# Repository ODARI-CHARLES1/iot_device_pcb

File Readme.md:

# IoT Device PCB

An IoT device PCB designed for logging and transmitting data.

## Schematic

## Specifications

- **Version:** V1.0.0
- **Date:** 2026-04-08
- **Company:** ODARI-DESIGNS

## Key Components

- **U1:** MCP73871 - Li-Ion/Li-Po Battery Charge Management Controller
- **J1:** USB Type-C Receptacle (USB 2.0, 16-pin)
- **J:** JST B2B-PH-K-S Connector (2-pin battery connection)
- **LEDs:** Status indicators (LTST-C170KRKT)

## Features

- USB-C power input
- Battery charging circuit (single-cell Li-Ion/Li-Po)
- LED status indicators
- Compact design for IoT applications

## License

MIT

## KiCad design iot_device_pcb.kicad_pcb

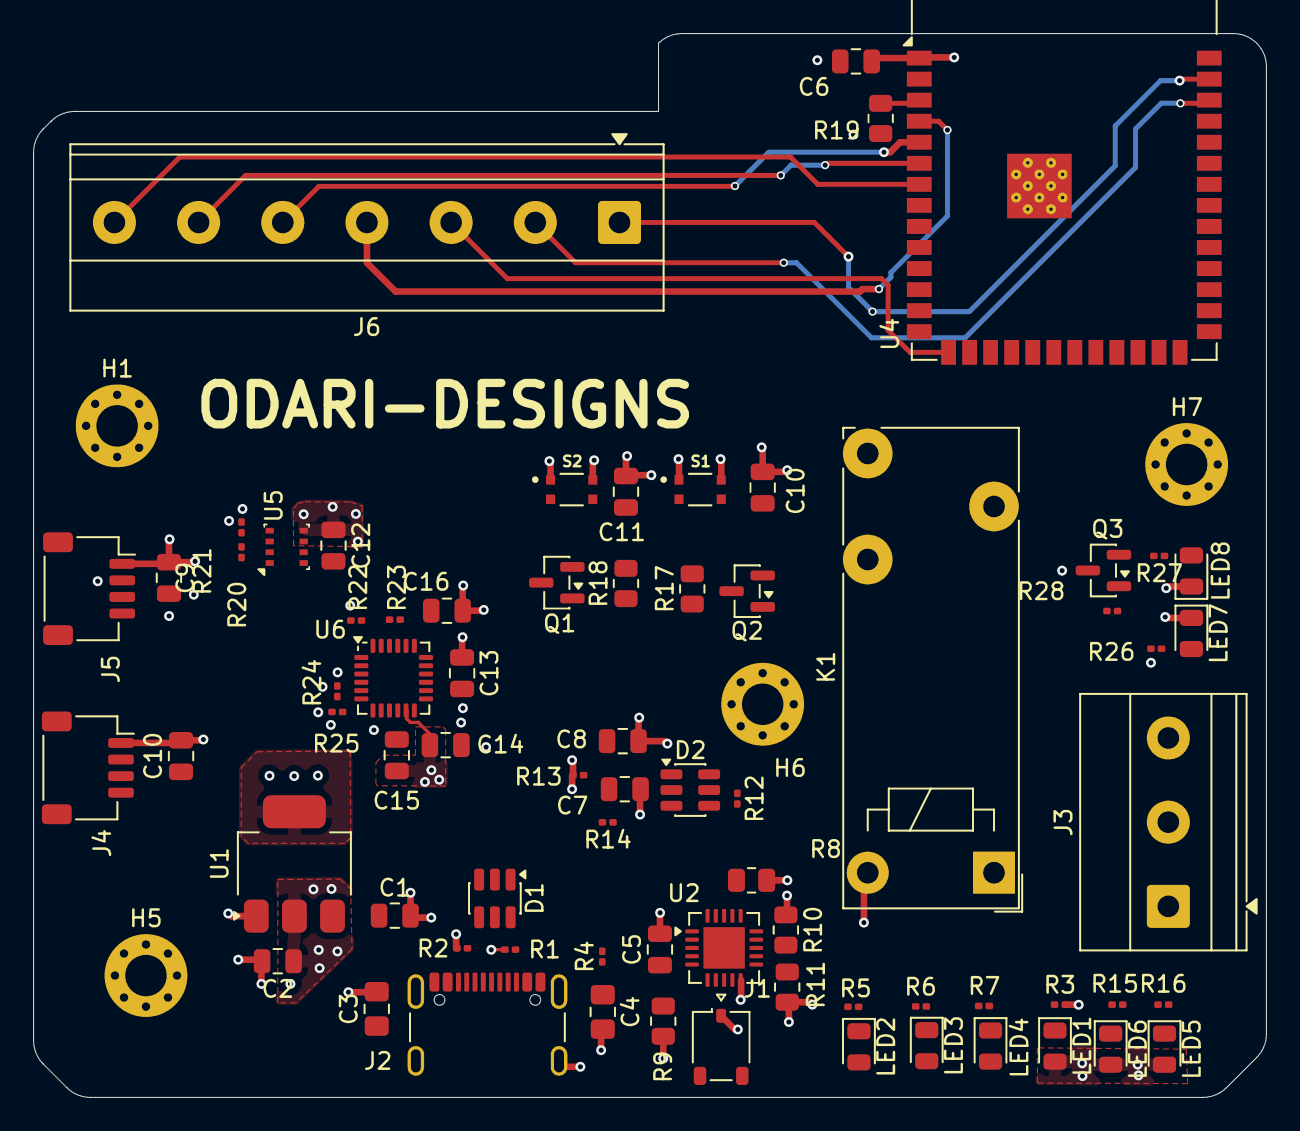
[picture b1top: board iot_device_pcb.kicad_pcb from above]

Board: 4 copper layers, 74.4 x 64.2 mm, 76 parts (0 on the bottom side), 49 nets.

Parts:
C1: 10u; C_0805_2012Metric
C2: 22u; C_0805_2012Metric
C3, C4: 470n; C_0805_2012Metric_Pad1.18x1.45mm_HandSolder
C5, C6, C8, C9, C10, C10#2, C12, C13, C14, C15: 0.1u; C_0805_2012Metric
C7, C11: 1u; C_0805_2012Metric
C16: 220p; C_0805_2012Metric
D1, D2: USBLC6-2SC6; SOT-23-6
H1, H5, H6, H7: MountingHole; MountingHole_2.5mm_Pad_Via
J1: B2B-PH-K-S_LF__SN_; JST_ACH_BM01B-ACHSS-A-GAN-ETF_1x01-1MP_P1.20mm_Vertical
J2: USB_C_Receptacle_USB2.0_16P; USB_C_Receptacle_GCT_USB4105-xx-A_16P_TopMnt_Horizontal
J3: Screw_Terminal_01x03; TerminalBlock_Phoenix_MKDS-1,5-3-5.08_1x03_P5.08mm_Horizont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
J4, J5: Conn_01x04_Pin; JST_SH_SM04B-SRSS-TB_1x04-1MP_P1.00mm_Horizontal
J6: Conn_01x07_Pin; TerminalBlock_Phoenix_MKDS-1,5-7-5.08_1x07_P5.08mm_Horizont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
K1: RAYEX-L90; Relay_1-Form-C_Schrack-RYII_RM3.2mm
LED1, LED4: LTST-C170KRKT; LED_0805_2012Metric
LED2, LED3, LED5, LED6, LED7, LED8: LTST-C170KGKT; LED_0805_2012Metric
Q1, Q2, Q3: BC817; SOT-23
R1, R2: 5.1k; R_0201_0603Metric
R3, R5, R6, R7, R15, R16, R26, R27, R28: 470R; R_0201_0603Metric
R4: 0; R_0201_0603Metric
R8, R9, R10, R11, R17, R18, R19: 10K; R_0805_2012Metric
R12: 22.1K; R_0201_0603Metric
R13, R24, R25: 47K5; R_0201_0603Metric
R14: 1k; R_0201_0603Metric
R20, R21, R22, R23: 4.7K; R_0201_0603Metric
S1, S2: USLPT2819DT2TR; SW_USLPT2819DT2TR
U1: AMS1117-3.3; SOT-223-3_TabPin2
U2: MCP73871; QFN-20-1EP_4x4mm_P0.5mm_EP2.5x2.5mm
U4: ESP32-S3-WROOM-1
U5: BME280; Bosch_LGA-8_2.5x2.5mm_P0.65mm_ClockwisePinNumbering
U6: MPU-6050; InvenSense_QFN-24_4x4mm_P0.5mm

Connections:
+3.3V: C2.1, C6.1, C8.2, C9.1, C10#2.1, C12.1, C13.1, C14.1, J4.2, J5.2, LED1.2, LED5.2, LED6.2, Q3.3 (C), R14.1, R19.1, R20.2, R21.2, R22.1, R23.1, R24.2, R25.2, R26.2, U1.2 (VO), U4.2 (3V3), U5.2 (CSB), U5.5 (SDO), U5.6 (VDDIO), U5.8 (VDD), U6.8 (VLOGIC), U6.13 (VDD)
+5V: C1.1, C4.1, LED2.2, LED3.2, LED4.2, R4.1, U1.3 (VI), U2.1 (OUT), U2.5 (THERM), U2.20 (OUT)
/Microcontroller-ESP32-S3-WROOM-1/BOOT: C10.1, Q2.2 (E), S1.3, S1.4, U4.27 (IO0)
/Microcontroller-ESP32-S3-WROOM-1/EN: C11.1, Q1.3 (C), R19.2, S2.3, S2.4, U4.3 (EN)
/Microcontroller-ESP32-S3-WROOM-1/GPIO1: J6.1, U4.39 (IO1)
/Microcontroller-ESP32-S3-WROOM-1/GPIO2: J6.2, U4.38 (IO2)
/Microcontroller-ESP32-S3-WROOM-1/GPIO3: J6.3, U4.15 (IO3)
/Microcontroller-ESP32-S3-WROOM-1/GPIO4: J6.4, U4.4 (IO4)
/Microcontroller-ESP32-S3-WROOM-1/GPIO5: J6.5, U4.5 (IO5)
/Microcontroller-ESP32-S3-WROOM-1/GPIO6: J6.6, U4.6 (IO6)
/Microcontroller-ESP32-S3-WROOM-1/GPIO7: J6.7, U4.7 (IO7)
/Microcontroller-ESP32-S3-WROOM-1/INT: U4.19 (IO11), U6.12 (INT)
/Microcontroller-ESP32-S3-WROOM-1/RELAY_FAN_GPIO: R28.2, U4.18 (IO10)
/Microcontroller-ESP32-S3-WROOM-1/RTS: Q1.2 (E), R18.2
/Microcontroller-ESP32-S3-WROOM-1/SCL: J4.4, J5.4, R21.1, R23.2, U4.17 (IO9), U5.4 (SCK), U6.23 (SCL)
/Microcontroller-ESP32-S3-WROOM-1/SDA: J4.3, J5.3, R20.1, R22.2, U4.12 (IO8), U5.3 (SDI), U6.24 (SDA)
/Microcontroller-ESP32-S3-WROOM-1/Sensors/XCL: R25.1, U6.7 (AUX_CL)
/Microcontroller-ESP32-S3-WROOM-1/Sensors/XDA: R24.1, U6.6 (AUX_DA)
/USBD+: D1.4 (I/O2), J2.B5 (CC2), R1.2
/USBD-: D1.6 (I/O1), D2.1 (I/O1), D2.3 (I/O2), J2.A5 (CC1), Q2.3 (C), R2.2, R17.2, U4.13 (USB_D-), U4.14 (USB_D+)
/VBAT: U2.14 (V_{BAT}), U2.15 (V_{BAT}), U2.16 (V_{BAT_SENSE})
GND: C1.2, C2.2, C3.2, C4.2, C5.2, C6.2, C7.2, C8.1, C9.2, C10.2, C10#2.2, C11.2, C12.2, C13.2, C14.2, C15.2, C16.2, D1.2 (GND), D2.2 (GND), J1.1 (1_1), J2.A1 (GND), J2.A12 (GND), J2.B1 (GND), J2.B12 (GND), J2.S1 (SHIELD), J4.1, J5.1, K1.A2, LED7.1, LED8.1, R1.1, R2.1, R3.1, R8.2, R9.2, R10.1, R11.1, R13.2, S1.1, S1.2, S2.1, S2.2, U1.1 (GND), U2.3 (SEL), U2.10 (V_{SS}), U2.11 (V_{SS}), U2.21 (V_{SS}), U4.1 (GND), U4.40 (GND), U4.41 (GND), U5.1 (GND), U5.7 (GND), U6.1 (CLKIN), U6.9 (AD0), U6.11 (FSYNC), U6.18 (GND)
unnamed: D1.1 (I/O1), J2.A7 (D-), J2.B7 (D-)
unnamed: D1.3 (I/O2), J2.A6 (D+), J2.B6 (D+)
unnamed: J3.1, K1.12
unnamed: J3.2, K1.14
unnamed: LED1.1, R3.2
unnamed: LED2.1, R5.2
unnamed: LED3.1, R6.2
unnamed: LED4.1, R7.2
unnamed: LED5.1, R16.2
unnamed: LED6.1, R15.2
unnamed: LED7.2, R26.1
unnamed: LED8.2, R27.1
unnamed: Q1.1 (B), R17.1
unnamed: Q2.1 (B), R18.1
unnamed: Q3.1 (B), R28.1
unnamed: K1.A1, Q3.2 (E), R27.2
unnamed: R8.1, U2.17 (CE)
unnamed: R10.2, U2.13 (PROG1)
unnamed: R11.2, U2.12 (PROG3)
unnamed: R6.1, U2.8 (STAT1/~LBO)
unnamed: R5.1, U2.7 (STAT2)
unnamed: R7.1, U2.6 (~PG)
unnamed: R9.1, U2.9 (~TE)
unnamed: C7.1, R12.2, R13.1
unnamed: C16.1, U6.20 (CPOUT)
unnamed: C15.1, U6.10 (REGOUT)
VBUS: C3.1, C5.1, D1.5 (VBUS), D2.5 (VBUS), J2.A4 (VBUS), J2.A9 (VBUS), J2.B4 (VBUS), J2.B9 (VBUS), R4.2, R12.1, U2.2 (VPCC), U2.4 (PROG2), U2.18 (IN), U2.19 (IN)

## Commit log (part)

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2026-04-06 chore: add .gitignore to ignore backup files
2026-04-06 chore(kicad): add lock file for power module schematic
2026-04-06 feat(iot): initialize PCB design for device hardware
    Add the foundational KiCad PCB file for the IoT device, establishing the board layout structure. This enables further development of the hardware components.
2026-04-06 build(kicad): introduce PCB project configuration for IoT hardware
    Establish the core .kicad_pro file to define project parameters, including design rules, layer setups, and electrical rule checks, facilitating streamlined PCB layout and verification processes for t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
2026-04-06 docs(iot): add project readme for IoT hardware
    Introduce a comprehensive Readme.md file detailing the IoT device project, including setup instructions, hardware specifications, and development guidelines to enhance project accessibility and colla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
2026-04-08 refactor(pcb): delete IoT device PCB file
2026-04-08 chore(settings): remove KiCad project local settings for IoT device PCB
    Clean up local configuration file that was no longer needed after project restructuring.
2026-04-08 feat(iot): add schematic for IoT device PCB including USB C connector
    Introduce the main schematic file for the IoT device PCB, featuring a USB C receptacle for connectivity and initial component layout. This restores the schematic design following previous cleanup and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
2026-04-08 chore(kicad): include auto-saved schematic backup for IoT device PCB
    Add a temporary backup file containing the auto-saved KiCad schematic to preserve recent changes during development. This ensures no loss of unsaved work on the IoT device PCB layout.
2026-04-11 chore(kicad): add auto-saved schematic backup for IoT device PCB
2026-04-11 feat(iot): add USB‑C connector and 3.3V regulator to schematic
    Add a USB‑C receptacle and an AMS1117‑3.3 LDO regulator to the iot_device_pcb schematic, along with a small capacitor symbol for decoupling. The autosave backup file was removed as part of the cleanu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
2026-04-11 refactor(kicad): remove auto‑save schematic backup
2026-04-11 docs(kicad): enrich component properties in iot_device_pcb schematic
    Added missing Footprint, Datasheet, Description, Manufacturer, part number, distributor links, and LCSC ID, and set exclude_from_sim to yes for improved component sourcing and simulation filtering.
2026-04-11 chore(kicad): add lock file for iot_device_pcb schematic
2026-04-11 feat(kicad): enable autosave for iot_device_pcb schematic
    Create a new autosave backup file `_autosave-iot_device_pcb.kicad_sch` that captures the current state of the iot_device_pcb schematic.
    This allows preservation of recent changes while editing the design, reducing accidental loss of progress.
2026-04-11 refactor(kicad): replace USB connector with LED in iot_device_pcb schematic
    Updated iot_device_pcb schematic by swapping USB connector for LED
    an LTST-C170KRKT LED component and updated its properties.
    Removed the lock flag and adjusted footprint and datasheet.
2026-04-11 refactor(kicad): enrich component metadata for R7 resistor and MCP73871
    Add detailed datasheet links, comprehensive descriptions, manufacturer information, and distributor URLs for the R7 resistor and MCP73871 battery charger in the schematic. These updates improve trace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
2026-04-11 docs(kicad): add schematic capture screenshot
    Add an updated screenshot of the iot_device_pcb schematic to assist designers in visualizing component placements and interconnections. This image supports documentation and quick reference usage.
2026-04-11 docs(readme): update readme with design specs and schematic
    Add version, date, company, component list, LED details, features and embed schematic image.
2026-04-13 chore(sch): update autosave reference to new schematic path
2026-04-13 refactor(kicad:schema): enrich capacitor properties and add microcontroller sheet
    Add comprehensive datasheet, description, manufacturer, part number,
    distributor links, and LCSC entry for the 0.1 µF MLCC. Create a dedicated
    sheet for the ESP32‑S3‑WROOM‑1 module with proper metadata and BOM
    attributes to improve hierarchy, sourcing, and simulation consistency.
2026-04-13 feat(kicad:schematics): add dedicated ESP32‑S3‑WROOM‑1 schematic
    Create a self‑contained kicad schematic file for the ESP32‑S3‑WROOM‑1 module.
    Includes datasheet, footprint, and BOM attributes to streamline reuse across
    the project and ensure a single source of truth for the module layout.
2026-04-13 feat(kicad:schematics): add USB D+/D- pins and routing for USB connections
    Provide necessary connections for USB D+ and D– pins,
    adding wires, labels, and pins to enable USB host functionality.
2026-04-13 refactor(kicad:schematics): update uuid of ESP32‑S3‑WROOM‑1 schematic
    Update schematic UUID to reflect the latest revision.
    Maintains consistency and avoids merge conflicts.
2026-04-13 chore(kicad:autosave): delete obsolete autosave file
    Removed the temporary autosave generated during a prior design session.
2026-04-20 chore: add auto-saved files list
2026-04-20 fix(kicad): restore schematic lock file
2026-04-20 chore(kicad): add autosave schematic file
2026-04-20 refactor(kicad): remove obsolete autosave schematic file
2026-04-20 refactor(schematic): update resistor footprints and component metadata
    Change resistor footprints from 0805 to 0201 metric and populate detailed component properties including manufacturer, part numbers, datasheets, and distributor links for improved BOM accuracy.
2026-04-20 fix(schematic): correct component part numbers and LCSC identifiers
    Update manufacturer part numbers and LCSC part codes to ensure correct component selection and procurement accuracy.
2026-04-20 docs(readme): reorder schematic section for better flow
2026-04-20 chore: remove auto-saved file
2026-04-27 chore(pcb): add accidental autosave schematic file
2026-04-27 refactor(pcb): remove redundant autosave schematic file
2026-04-27 chore(pcb): add lock file for KiCad schematic
2026-04-27 feat(pcb): add actuators schematic
2026-04-27 fix(schematic): replace power symbol with BC817 transistor
    Replaces the redundant +3.3V power symbol with a BC817 NPN transistor component, including proper footprint (SOT-23), datasheet link, and pin definitions.
2026-04-27 feat(sensors): add sensors schematic file
2026-04-27 chore(pcb): update project metadata to include new schematic modules
2026-04-27 Chore(Readme): add new schematic image capture
2026-05-04 Implement feature X to enhance user experience and fix bug Y in module Z
2026-05-04 chore: update autosave file to reflect new sensor schematic
2026-05-04 Implement feature X to enhance user experience and optimize performance
2026-05-04 chore: add initial fp-info-cache file
2026-05-04 feat(hw): add iot device pcb design
2026-05-04 feat(hw): enhance design settings and rules for improved PCB layout and validation
2026-05-04 feat(hw): update component references for improved clarity in PCB design
2026-05-04 chore: remove lock file for improved project management
2026-05-04 feat(hw): update component references for consistency in PCB design
2026-05-07 chore: add auto-saved file to repository
2026-05-07 chore(pcb): add schematic lock file
2026-05-07 feat(hw): add connector symbol to display schematic
    Add the Conn_01x04_Pin symbol to the Display schematic to support
    the integration of the 4-pin connector.
2026-05-07 refactor(sensors): adjust schematic component positioning
    Shift the placement of the +3.3V power symbol and associated junctions
    in the Sensors schematic to improve layout alignment.
2026-05-07 feat(schematic): add initial display schematic with connector symbols
2026-05-07 feat(pcb): add autosaved schematic state
2026-05-07 chore(pcb): remove temporary autosave schematic file
2026-05-07 refactor(pcb): adjust schematic rectangle coordinates
2026-05-07 fix(sch): reposition connector J3 and associated wires
2026-05-07 feat(sch): add power symbols and connector label
    Add +3.3V and GND power symbols to the Display schematic and include
    a rectangle and text label for the OLED_DISPLAY_CONNECTOR.
2026-05-07 feat(symbols): add Amphenol GSD090012SEU SD card socket
    Add the KiCad symbol library entry for the GSD090012SEU Micro SD and
    SD Card Socket from Amphenol.
2026-05-07 fix(sch): adjust wire endpoints and add labels for SDA and SCL
2026-05-07 feat(sch): add additional wire connections and labels for SDA, SCL, and INT
2026-05-07 chore: remove lock file for schematic
2026-05-13 feat(sch): add LTST-C170KRKT LED symbol to actuators schematic
2026-05-13 refactor(sch): replace +3.3V power symbol with 7-pin connector
    Replaces the global +3.3V power symbol with a physical 1x07 connector symbol in the Display schematic.
2026-05-13 feat(pcb): update netlist and component placement for iot_device_pcb
2026-05-13 refactor(pcb): reconfigure netclasses and design rules
    Update the KiCad project configuration to redefine netclass patterns
    and establish default design rule parameters for differential pairs,
    track widths, and via dimensions. Reorganizes netclass naming
    conventions for power and ground rails.
2026-05-13 chore(sch): update footprint for single-pin connector
    Replace the existing JST B2B-PH footprint with a JST ACH BM01B
    vertical 1x01 connector to match updated hardware specifications.
2026-05-13 fix(sch): reroute sensor wiring and update component references
    Adjusted wire connections and component labels in the sensors schematic to correct routing paths and ensure proper connectivity. Updated power reference identifiers to maintain consistency with the r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
2026-05-18 chore(pcb): update active layer and visible layers in project file
2026-05-18 feat(sch): add mounting holes to schematic
2026-05-18 fix(sch): update component and power reference designators
    Update various component references (C14, C15, C16) and power net labels
    (#PWR050, #PWR051, #PWR053, #PWR055, #PWR056) in the Sensors schematic
    to ensure correct netlist consistency.
2026-05-25 feat(pcb): add internal layers and update stackup
    Add two new internal copper layers (In1.Cu and In2.Cu) and define the full PCB stackup including dielectric materials and thicknesses. Also includes minor component placement adjustments and net upda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
2026-05-25 chore(pcb): update editor view settings and column layout
    Adjust the active layer index and modify the grid column widths and ordering to optimize the workspace layout.
2026-05-25 refactor(sch): remove redundant GPIO labels
    Remove multiple duplicate "GPIO" text labels from the schematic to clean up the drawing and prevent overlapping text elements.
2026-06-01 refactor(sch): update symbol metadata and schema version
    Migrate schematic to KiCad 20260306 and generator 10.0.
    Standardize symbol properties by adding visibility controls,
    autoplace settings, and updating datasheet references.
2026-06-01 chore(pcb): upgrade KiCad file format and plot settings
    Update the PCB file to KiCad version 20260206 and generator 10.0.
    Refactor plot parameters to include explicit tenting, covering,
    plugging, and capping settings, and clean up legacy HPGL parameters.
2026-06-01 build(pcb): update editor preferences and workspace configuration
    Adjust column widths, layer visibility, and selection filters in the
    PCB editor settings. Enable Git integration and update prototype
    zone fill defaults.
2026-06-01 build(sch): upgrade kicad version and update symbol properties
    Update the schematic file to KiCad version 20260306 and generator
    version 10.0. This includes updating symbol metadata, adjusting pin
    positions, and refining property visibility and placement settings
    for various components.
2026-06-01 refactor(sch): adjust symbol properties and pin mapping
    Update component metadata and pin assignments within the schematic to
    improve property management and ensure correct pin numbering. This
    includes setting visibility flags for properties and correcting
    pin positions for specific symbols.
